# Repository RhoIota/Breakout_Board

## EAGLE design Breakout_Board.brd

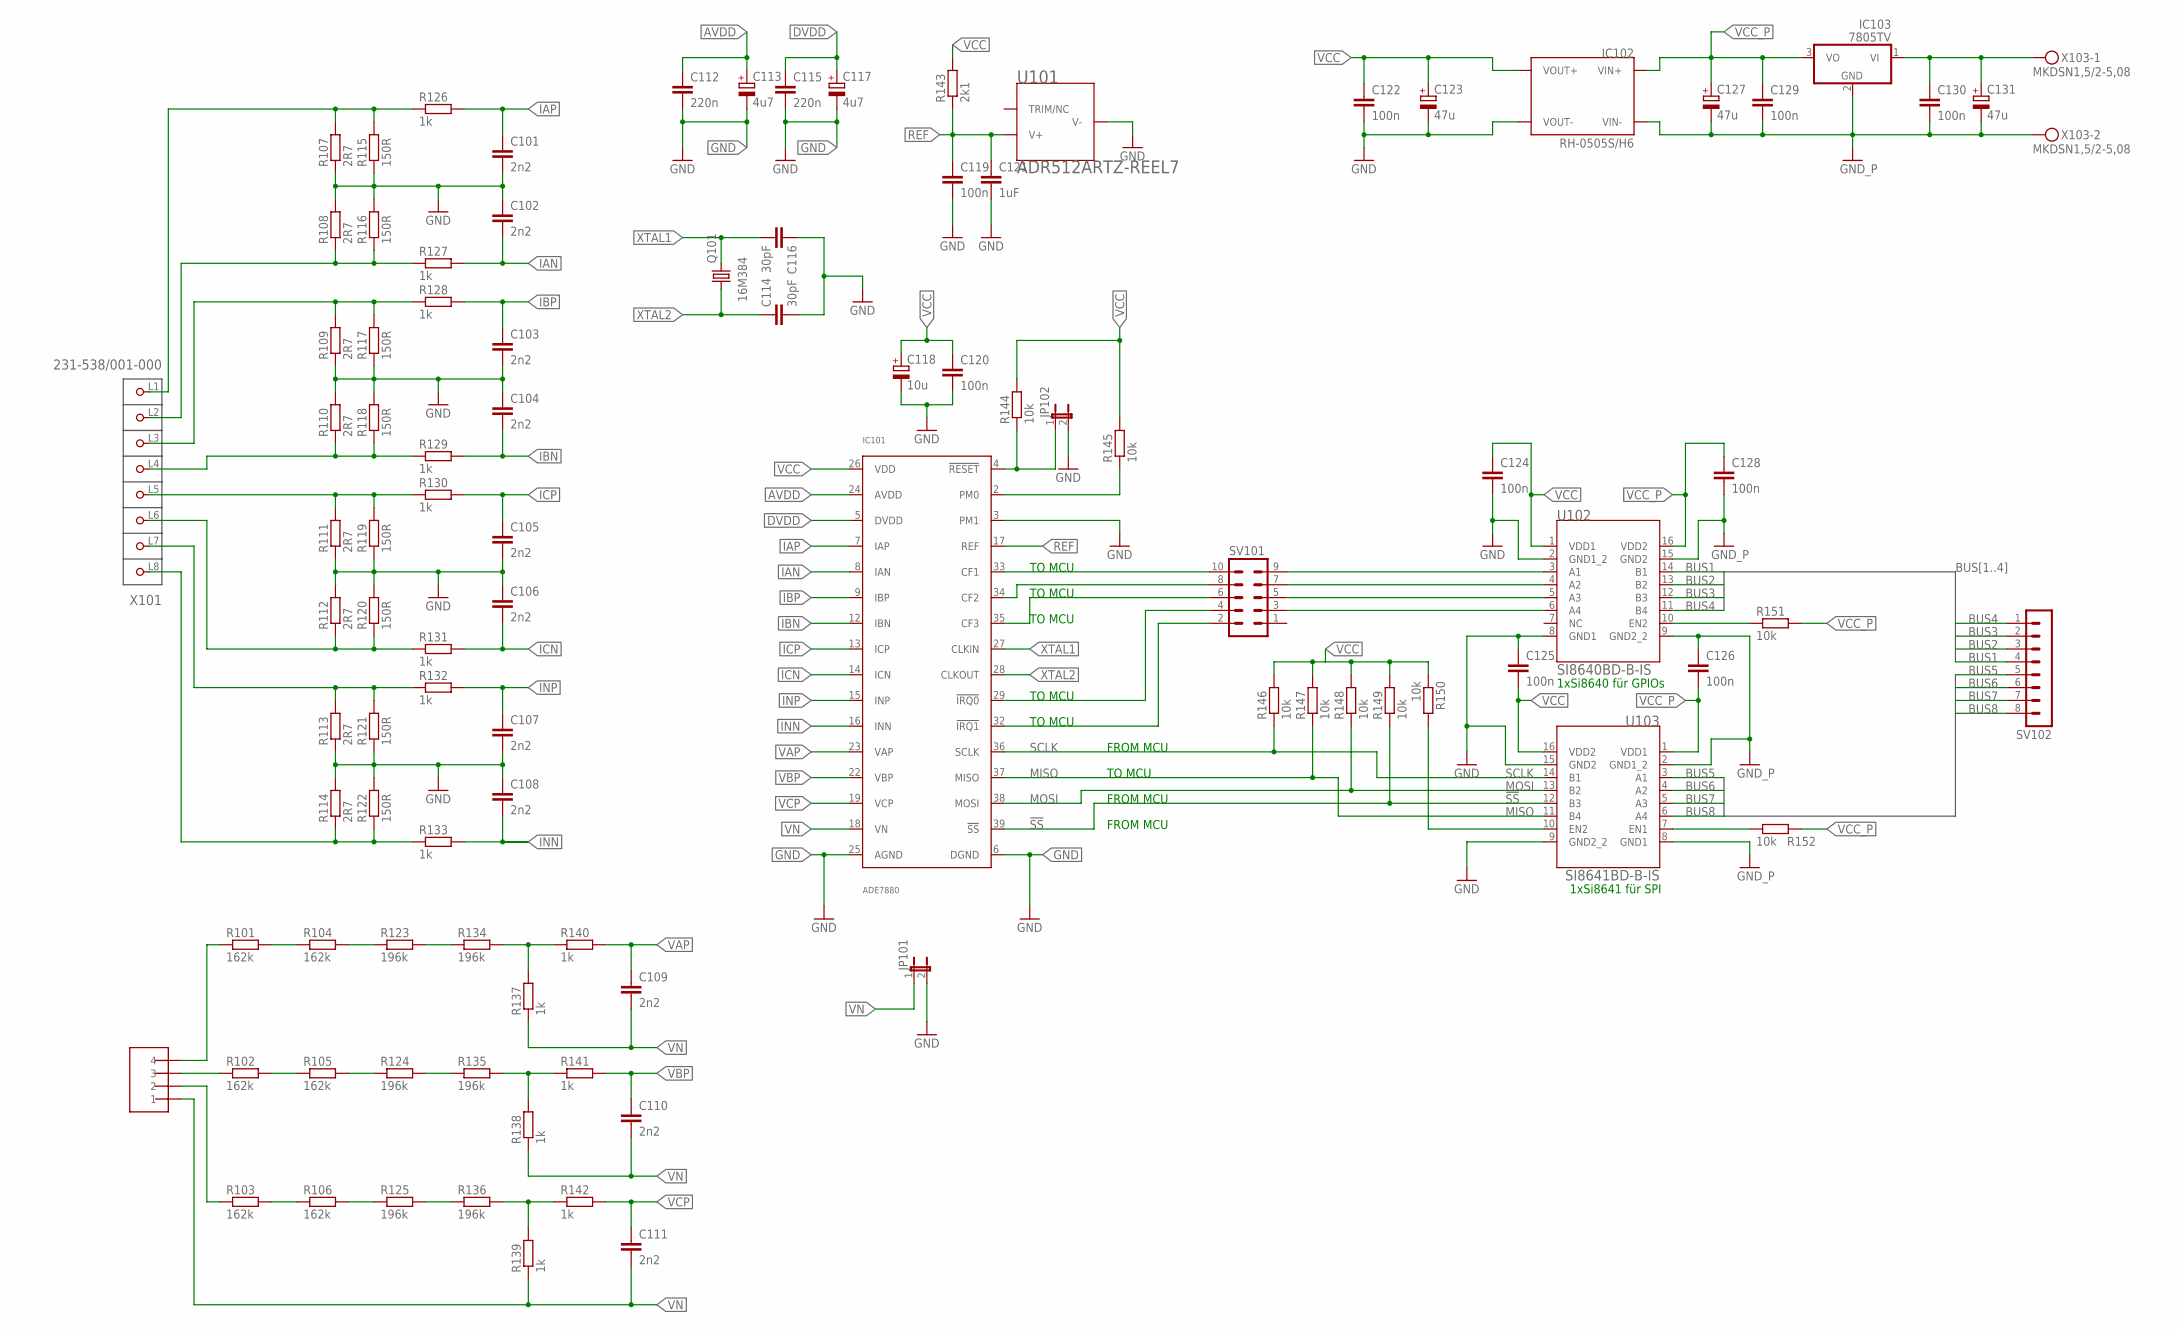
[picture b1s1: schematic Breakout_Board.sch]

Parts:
C101, C102, C103, C104, C105, C106, C107, C108, C109, C110, C111: 2n2; C0603K
C112, C115: 220n; C0603K
C113, C117: 4u7; PANASONIC_B
C114, C116: 30pF; C0603K
C118: 10u; PANASONIC_B
C119, C120, C122, C124, C125, C126, C128, C129, C130: 100n; C0603K
C121: 1uF; C0603K
C123, C127, C131: 47u; PANASONIC_D
IC101: ADE7880; BREAKOUT40P
IC102: RH-0505S/H6; RH/H6
IC103: 7805TV; TO220V
JP101, JP102: JP1E; JP1
Q101: 16M384; HC49UP
R101, R102, R103, R104, R105, R106: 162k; R0805
R107, R108, R109, R110, R111, R112, R113, R114: 2R7; R0805
R115, R116, R117, R118, R119, R120, R121, R122: 150R; R0805
R123, R124, R125, R134, R135, R136: 196k; R0805
R126, R127, R128, R129, R130, R131, R132, R133, R140, R141, R142: 1k; R0603
R137, R138, R139: 1k; R0805
R143: 2k1; R0603
R144, R145, R146, R147, R148, R149, R150, R151, R152: 10k; R0603
SV101: MA05-2
SV102: MA08-1
U101: ADR512ARTZ-REEL7; RT_3
U102: SI8640BD-B-IS; SOIC-16W
U103: SI8641BD-B-IS; SOIC-16W
X101: 231-538/001-000; P-231-538/001-000
X102: STL266-04; 7.62MM-4POL
X103: MKDSN1,5/2-5,08

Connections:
!SS: IC101.39 (!SS), R149.1, U103.12 (B3)
AVDD: C112.1, C113.+, IC101.24 (AVDD)
BUS1: SV102.4, U102.14 (B1)
BUS2: SV102.3, U102.13 (B2)
BUS3: SV102.2, U102.12 (B3)
BUS4: SV102.1, U102.11 (B4)
BUS5: SV102.5, U103.3 (A1)
BUS6: SV102.6, U103.4 (A2)
BUS7: SV102.7, U103.5 (A3)
BUS8: SV102.8, U103.6 (A4)
DVDD: C115.1, C117.+, IC101.5 (DVDD)
GND: C101.2, C102.1, C103.2, C104.1, C105.2, C106.1, C107.2, C108.1, C112.2, C113.-, C114.2, C115.2, C116.1, C117.-, C118.-, C119.2, C120.2, C121.2, C122.2, C123.-, C124.2, C125.1, IC101.3 (PM1), IC101.6 (DGND), IC101.25 (AGND), IC102.P$3 (VOUT-), JP101.2, JP102.2, R107.1, R108.2, R109.1, R110.2, R111.1, R112.2, R113.1, R114.2, R115.1, R116.2, R117.1, R118.2, R119.1, R120.2, R121.1, R122.2, U101.2 (V-), U102.2 (GND1_2), U102.8 (GND1), U103.9 (GND2_2), U103.15 (GND2)
GND_P: C126.1, C127.-, C128.2, C129.2, C130.2, C131.-, IC102.P$2 (VIN-), IC103.2 (GND), U102.9 (GND2_2), U102.15 (GND2), U103.2 (GND1_2), U103.8 (GND1), X103.2
IAN: C102.2, IC101.8 (IAN), R127.2
IAP: C101.1, IC101.7 (IAP), R126.2
IBN: C104.2, IC101.12 (IBN), R129.2
IBP: C103.1, IC101.9 (IBP), R128.2
ICN: C106.2, IC101.14 (ICN), R131.2
ICP: C105.1, IC101.13 (ICP), R130.2
INH: R113.2, R121.2, R132.1, X101.L7 (P7)
INL: R114.1, R122.1, R133.1, X101.L8 (P8)
INN: C108.2, IC101.16 (INN), R133.2
INP: C107.1, IC101.15 (INP), R132.2
L1H: R107.2, R115.2, R126.1, X101.L1 (P1)
L1L: R108.1, R116.1, R127.1, X101.L2 (P2)
L2H: R109.2, R117.2, R128.1, X101.L3 (P3)
L2L: R110.1, R118.1, R129.1, X101.L4 (P4)
L3H: R111.2, R119.2, R130.1, X101.L5 (P5)
L3L: R112.1, R120.1, R131.1, X101.L6 (P6)
MISO: IC101.37 (MISO), R147.1, U103.11 (B4)
MOSI: IC101.38 (MOSI), R148.1, U103.13 (B2)
unnamed: R101.2, R104.1
unnamed: R104.2, R123.1
unnamed: R123.2, R134.1
unnamed: R134.2, R137.2, R140.1
unnamed: R101.1, X102.P$4 (4)
unnamed: R102.2, R105.1
unnamed: R105.2, R124.1
unnamed: R124.2, R135.1
unnamed: R135.2, R138.2, R141.1
unnamed: R102.1, X102.P$3 (3)
unnamed: R103.2, R106.1
unnamed: R106.2, R125.1
unnamed: R125.2, R136.1
unnamed: R136.2, R139.2, R142.1
unnamed: R103.1, X102.P$2 (2)
unnamed: R150.2, U103.10 (EN2)
unnamed: IC101.2 (PM0), R145.1
unnamed: IC101.4 (!RESET), JP102.1, R144.1
unnamed: SV101.9, U102.3 (A1)
unnamed: SV101.7, U102.4 (A2)
unnamed: SV101.5, U102.5 (A3)
unnamed: SV101.3, U102.6 (A4)
unnamed: IC101.33 (CF1), SV101.10
unnamed: IC101.34 (CF2), SV101.8
unnamed: IC101.35 (CF3), SV101.6
unnamed: IC101.29 (!IRQ0), SV101.4
unnamed: IC101.32 (!IRQ1), SV101.2
unnamed: R152.1, U103.7 (EN1)
unnamed: R151.1, U102.10 (EN2)
unnamed: C130.1, C131.+, IC103.1 (VI), X103.1
REF: C119.1, C121.1, IC101.17 (REF), R143.1, U101.1 (V+)
SCLK: IC101.36 (SCLK), R146.1, U103.14 (B1)
VAP: C109.1, IC101.23 (VAP), R140.2
VBP: C110.1, IC101.22 (VBP), R141.2
VCC: C118.+, C120.1, C122.1, C123.+, C124.1, C125.2, IC101.26 (VDD), IC102.P$5 (VOUT+), R143.2, R144.2, R145.2, R146.2, R147.2, R148.2, R149.2, R150.1, U102.1 (VDD1), U103.16 (VDD2)
VCC_P: C126.2, C127.+, C128.1, C129.1, IC102.P$1 (VIN+), IC103.3 (VO), R151.2, R152.2, U102.16 (VDD2), U103.1 (VDD1)
VCP: C111.1, IC101.19 (VCP), R142.2
VN: C109.2, C110.2, C111.2, IC101.18 (VN), JP101.1, R137.1, R138.1, R139.1, X102.P$1 (1)
XTAL1: C116.2, IC101.27 (CLKIN), Q101.2
XTAL2: C114.1, IC101.28 (CLKOUT), Q101.1

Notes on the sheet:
TO MCU
FROM MCU
1xSi8640 für GPIOs
1xSi8641 für SPI

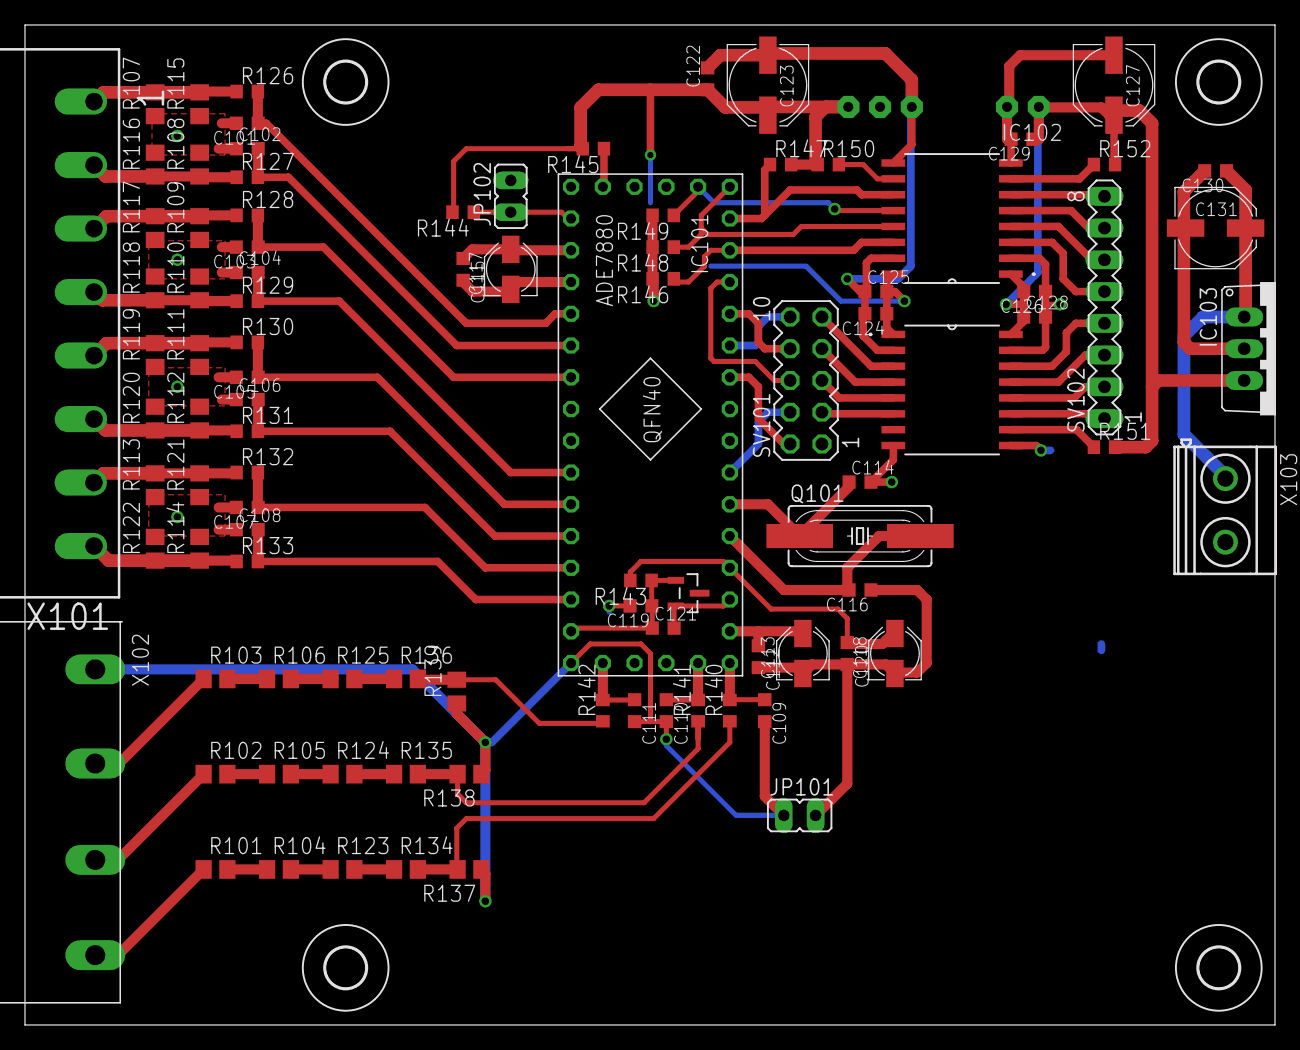
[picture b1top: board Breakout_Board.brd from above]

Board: 2 copper layers, 100.0 x 80.0 mm, 101 parts (0 on the bottom side), 71 nets.

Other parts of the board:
U$1, U$2, U$3, U$4: 3,2

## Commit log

2016-10-21 :lollipop: Added .gitattributes & .gitignore files
2016-10-21 new files
2016-10-22 test
2016-10-23 deleted the temp files
2016-11-06 Board layout updated
2016-11-06 Board layout finished without checking DRC
2016-11-12 First official release!
2016-12-21 A1 schematic and layout
2017-07-21 -updated sch and brd, added pdf files
